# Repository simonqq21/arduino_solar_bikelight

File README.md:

# Arduino Solar Rear Bicycle Light 
## Main Hardware Components
- Arduino Nano
- 6V 1W solar panel 
- TP4056 li-ion charger with BMS chip 
- 18650 battery holder with 18650 battery x1  
- 10k resistor (charging input voltage divider)
- 50k resistor (charging input voltage divider) 
- 10k resistor (battery voltage divider)
- 50k resistor (battery panel voltage divider) 
- Diffused red LED x5 (dim light, one as a charging indicator when turned off)
- 150R resistor x5
- Clear red LED x4 (bright light) 
- 150R resistor x4
- 2N3904 NPN transistor x2
- 10k resistor x2
- Momentary pushbutton 

## Things to calculate/ measure: 
solar panel no-load voltage 
solar panel max current
expected battery charge time 
expected runtime 
voltage divider resistances 

assume 6V max voltage input, 5V max voltage output 
6 * r2 / (r1 + r2) = 5 
6 * r2 = 5 * (r1 + r2)
6 * r2 = 5 * r1 + 5 * r2 
r2 = 5 * r1 
The current through the voltage divider must be minimal. 
if r2 is 50k, r1 is 10k.

LED current limiting resistors 
diffused LED 

Li-ion voltage max 4.2V 
LED current = 20mA
(4.2-2.1)/0.02 = 105 R resistor minimum

clear LED

Li-ion voltage max 4.2V 
LED current = 30mA
(4.2-2.1)/0.03 = 70 R resistor minimum

Calculations for the voltage divider resistances when using the internal 1.1V Vref 

Min input (PV panel and USB charger) voltage: 0V
Max input (PV panel and USB charger) voltage: 7V
max USB charger voltage: 5V
max PV panel voltage: ~7V - 0.3V = 6.7V (0.3V voltage drop from the diode)
Max input (PV panel and USB charger) voltage: 6.7 ~= 7V
Vin = 7V 
Vout = 1.1V
7* r2/(r1+r2) = 1.1
7r2 = 1.1r1 + 1.1r2 
5.9r2 = 1.1r1 
r1 = 5.9r2/1.1
r2 = 10k 
r1 = 53636.364 ~= 53k 

Min battery voltage: 3.0V
Max battery voltage: 4.2V
Vin = 4.2V
Vout = 1.1V
4.2* r2/(r1+r2) = 1.1 
4.2r2 = 1.1r1 + 1.1r2 
3.1r2 = 1.1r1
r1 = 3.1r2 / 1.1 
r2 = 10k  
r1 = 28181.818 ~= 28k 

Battery voltage divider 
r1 = 50k 
r2 = 10k 
input voltage min: 3.0V
input voltage max: 4.2V
conversion factor = 10k/(50k+10k) = 1/6 
3.0V*1/6 = 0.5V 
4.2V*1/6 = 0.7V
0.5/1.1*1023=465 
0.7/1.1*1023=651

Charging input voltage divider 
r1 = 50k 
r2 = 10k 
input voltage min: 0.0V
input voltage max: 7.0V
input voltage threshold: 4.8V 
conversion factor = 10k/(50k+10k) = 1/6 
0.0V*1/6 = 0V 
7.0V*1/6 = 1.167V
4.8V*1/6 = 0.8V  
1.167/1.1*1023=1023 (capped at 1023, but it doesn't matter anyways)
0.8/1.1*1023=744

# Power Consumption 
power consumption in Off Mode (quiescent current) 35uA
power consumption in Low Mode 78mA
power consumption in High Mode 118mA

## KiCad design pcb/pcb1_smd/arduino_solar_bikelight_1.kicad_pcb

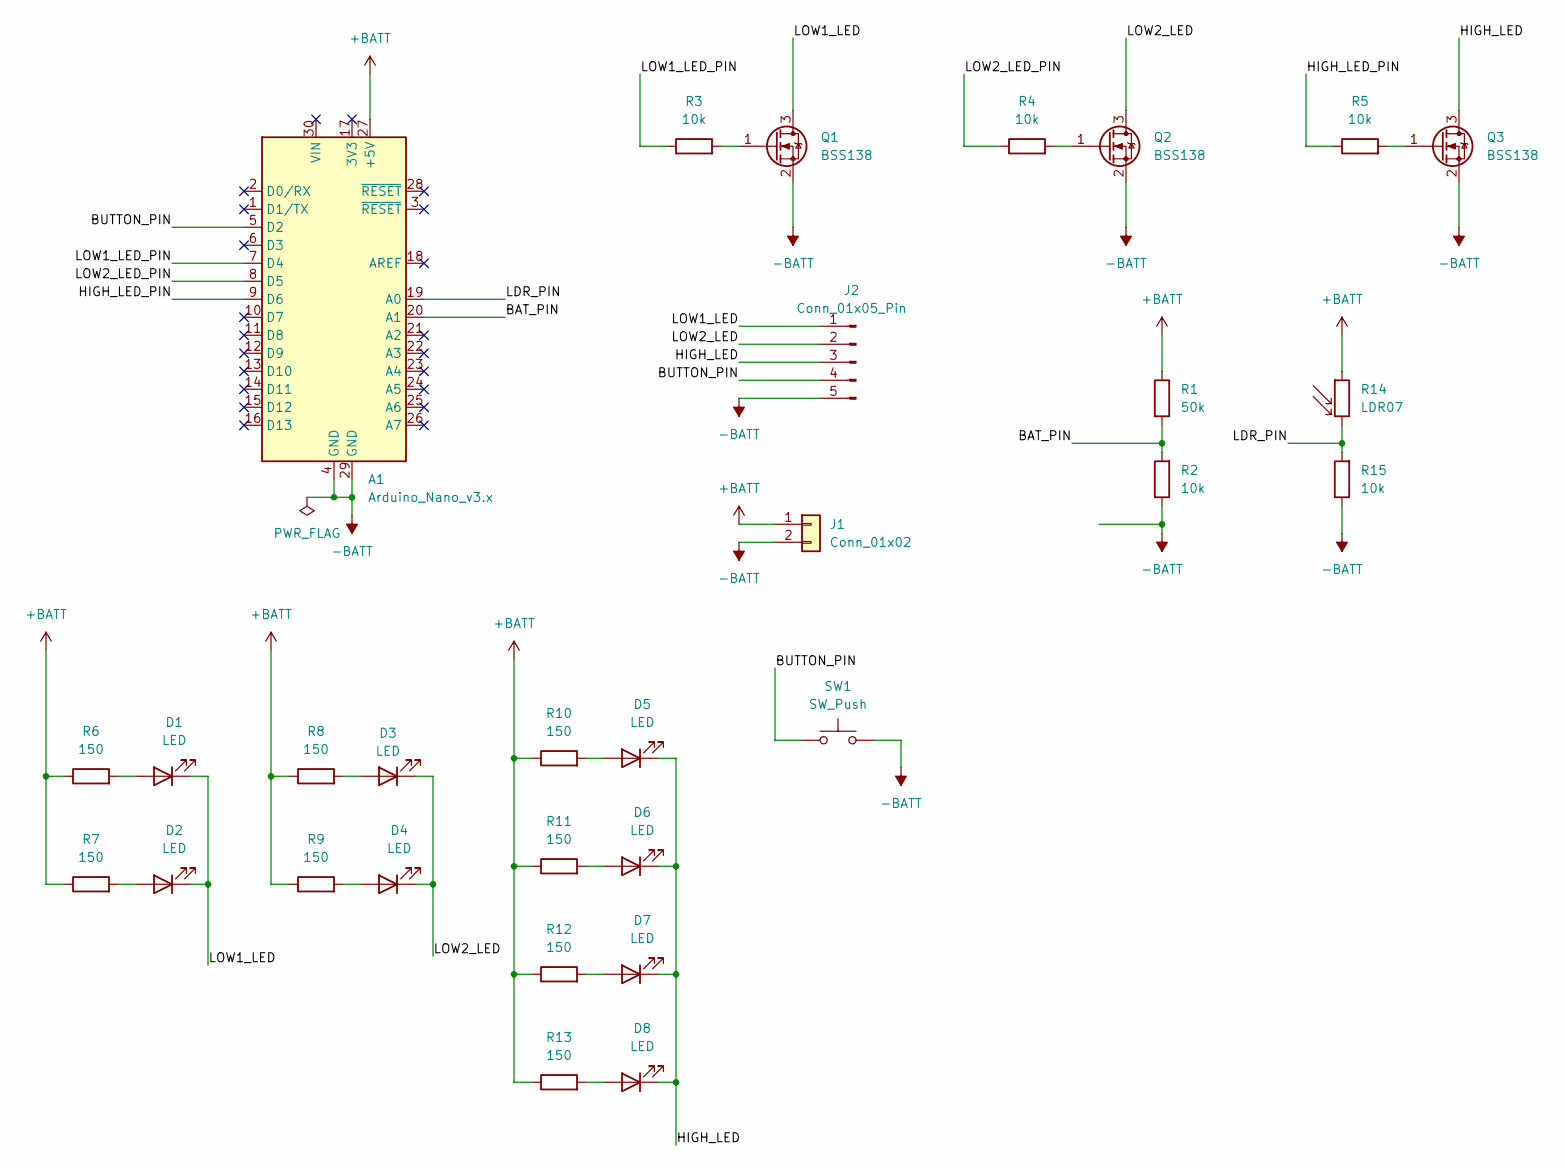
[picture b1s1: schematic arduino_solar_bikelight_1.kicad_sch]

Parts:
A1: Arduino_Nano_v3.x; Arduino_Nano
D1, D2, D3, D4, D5, D6, D7, D8: LED; LED_D5.0mm
J1: Conn_01x02; JST_XH_B2B-XH-AM_1x02_P2.50mm_Vertical
J2: Conn_01x05_Pin; PinHeader_1x05_P2.54mm_Vertical
Q1, Q2, Q3: BSS138; SOT-23; LCSC C78284
R1: 50k; R_0805_2012Metric_Pad1.20x1.40mm_HandSolder; LCSC C17737
R2, R3, R4, R5, R15: 10k; R_0805_2012Metric_Pad1.20x1.40mm_HandSolder; LCSC C17414
R6, R7, R8, R9, R10, R11, R12, R13: 150; R_0805_2012Metric_Pad1.20x1.40mm_HandSolder; LCSC C17471
R14: LDR07; R_LDR_5.1x4.3mm_P3.4mm_Vertical
SW1: SW_Push; SW_SPST_Omron_B3F-40xx

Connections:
+BATT: A1.27 (+5V), J1.1, R1.1, R6.1, R7.1, R8.1, R9.1, R10.1, R11.1, R12.1, R13.1, R14.1
-BATT: A1.4 (GND), A1.29 (GND), J1.2, J2.5, Q1.2 (S), Q2.2 (S), Q3.2 (S), R2.1, R15.1, SW1.2
/BAT_PIN: A1.20 (A1), R1.2, R2.2
/BUTTON_PIN: A1.5 (D2), J2.4, SW1.1
/HIGH_LED: D5.1 (K), D6.1 (K), D7.1 (K), D8.1 (K), J2.3, Q3.3 (D)
/HIGH_LED_PIN: A1.9 (D6), R5.1
/LDR_PIN: A1.19 (A0), R14.2, R15.2
/LOW1_LED: D1.1 (K), D2.1 (K), J2.1, Q1.3 (D)
/LOW1_LED_PIN: A1.7 (D4), R3.1
/LOW2_LED: D3.1 (K), D4.1 (K), J2.2, Q2.3 (D)
/LOW2_LED_PIN: A1.8 (D5), R4.1
unnamed: D1.2 (A), R6.2
unnamed: D2.2 (A), R7.2
unnamed: D3.2 (A), R8.2
unnamed: D4.2 (A), R9.2
unnamed: D5.2 (A), R10.2
unnamed: D6.2 (A), R11.2
unnamed: D7.2 (A), R12.2
unnamed: D8.2 (A), R13.2
unnamed: Q1.1 (G), R3.2
unnamed: Q2.1 (G), R4.2
unnamed: Q3.1 (G), R5.2

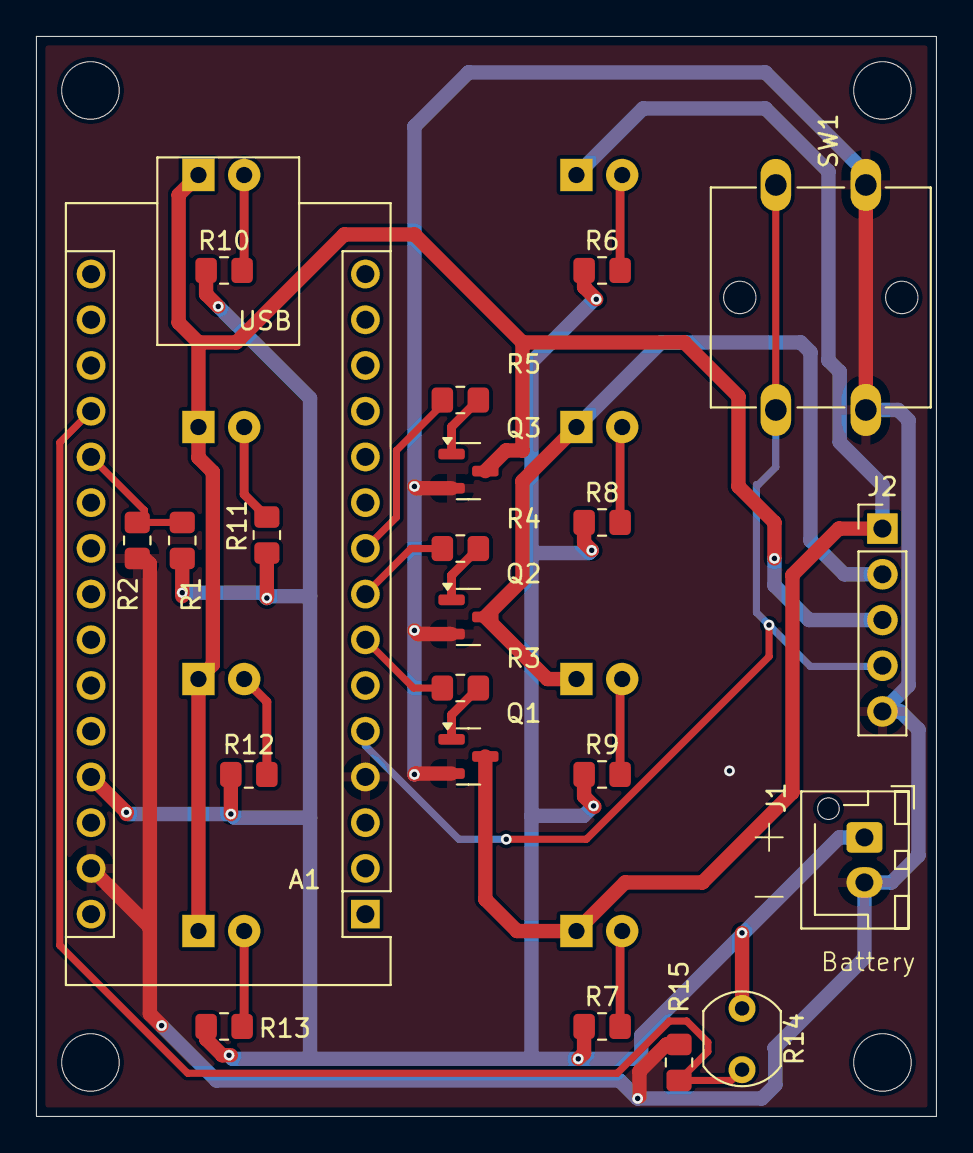
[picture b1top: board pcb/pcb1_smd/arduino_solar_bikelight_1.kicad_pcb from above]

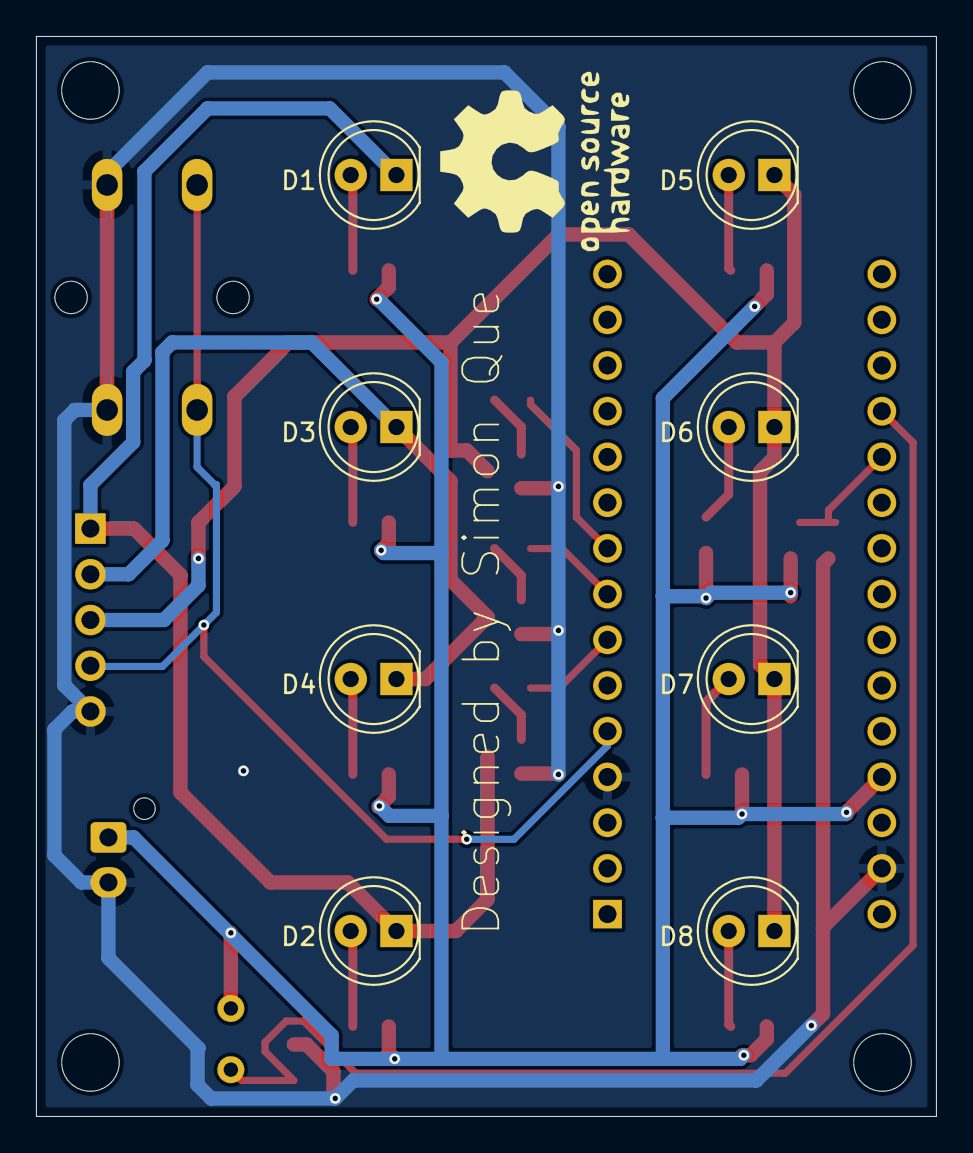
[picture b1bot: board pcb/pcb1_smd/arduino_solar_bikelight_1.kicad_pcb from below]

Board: 2 copper layers, 50.0 x 60.0 mm, 30 parts (8 on the bottom side), 22 nets.

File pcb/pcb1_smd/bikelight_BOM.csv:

Designator,Comment,Footprint,LCSC
"R6,R7,R8,R9,R10,R11,R12,R13",150,Resistor_SMD:R_0805_2012Metric_Pad1.20x1.40mm_HandSolder,C17471
"R2,R3,R4,R5",10k,Resistor_SMD:R_0805_2012Metric_Pad1.20x1.40mm_HandSolder,C17414
R1,50k,Resistor_SMD:R_0805_2012Metric_Pad1.20x1.40mm_HandSolder,C17737
A1,Arduino_Nano_v3.x,Module:Arduino_Nano,
"Q1,Q2,Q3",BSS138,Package_TO_SOT_SMD:SOT-23,C78284
J1,Conn_01x02,Connector_JST:JST_XH_B2B-XH-AM_1x02_P2.50mm_Vertical,
J2,Conn_01x05_Pin,Connector_PinHeader_2.54mm:PinHeader_1x05_P2.54mm_Vertical,
"D1,D2,D3,D4,D5,D6,D7,D8",LED,LED_THT:LED_D5.0mm,
SW1,SW_Push,Button_Switch_THT:SW_SPST_Omron_B3F-40xx,

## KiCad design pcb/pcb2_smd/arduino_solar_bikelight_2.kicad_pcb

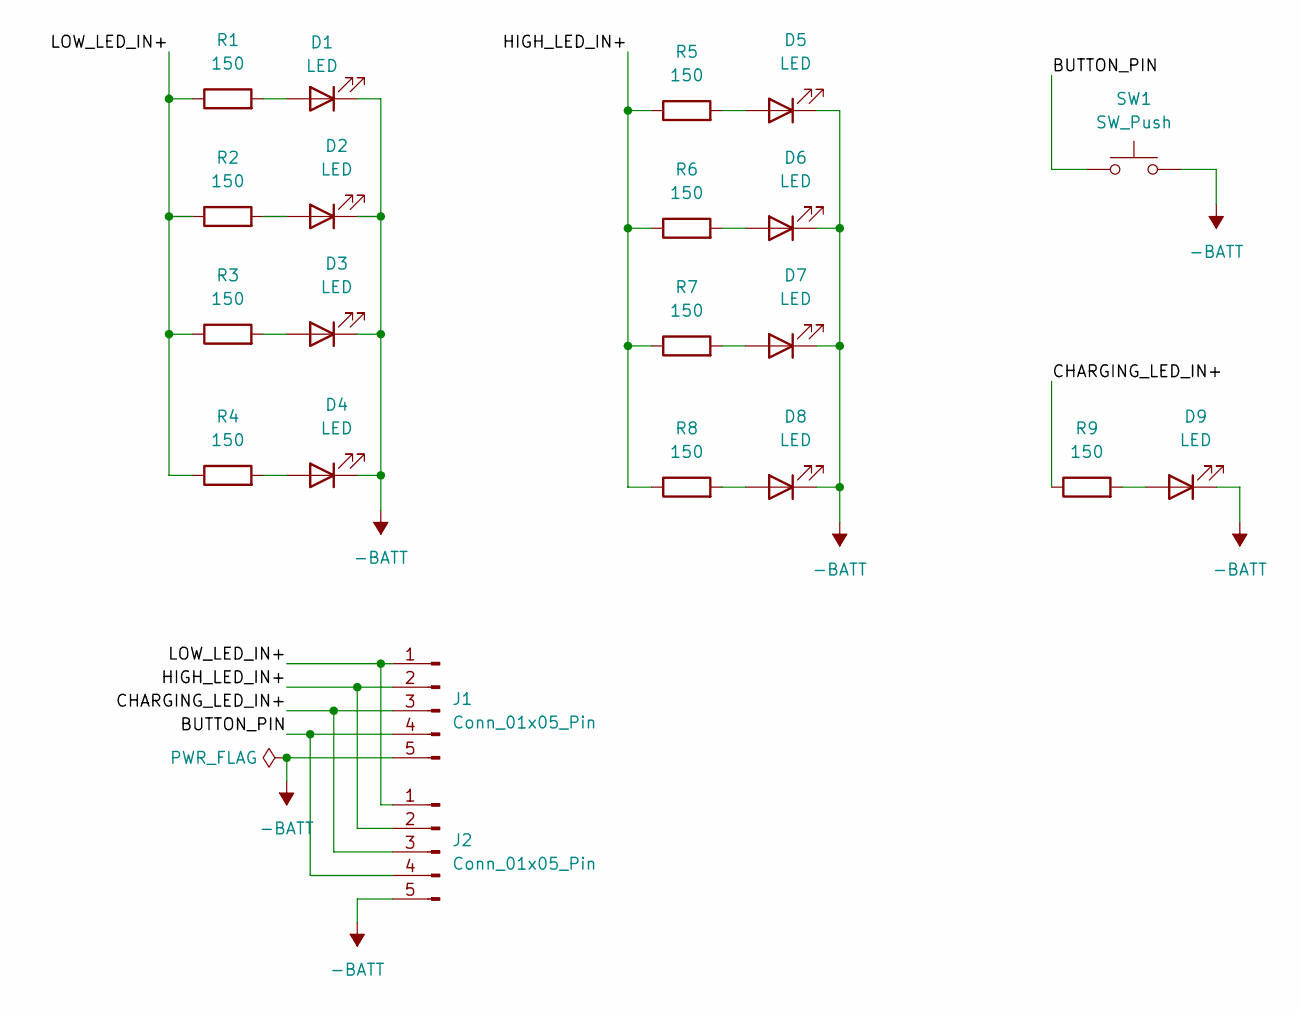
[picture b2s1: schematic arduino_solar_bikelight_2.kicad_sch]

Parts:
D1, D2, D3, D4, D5, D6, D7, D8, D9: LED; LED_D5.0mm
J1, J2: Conn_01x05_Pin; PinSocket_1x05_P2.54mm_Vertical
R1, R2, R3, R4, R5, R6, R7, R8, R9: 150; R_Axial_DIN0207_L6.3mm_D2.5mm_P10.16mm_Horizontal
SW1: SW_Push; SW_SPST_Omron_B3F-40xx

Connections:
-BATT: D1.1 (K), D2.1 (K), D3.1 (K), D4.1 (K), D5.1 (K), D6.1 (K), D7.1 (K), D8.1 (K), D9.1 (K), J1.5, J2.5, SW1.2
/BUTTON_PIN: J1.4, J2.4, SW1.1
/CHARGING_LED_IN+: J1.3, J2.3, R9.1
/HIGH_LED_IN+: J1.2, J2.2, R5.1, R6.1, R7.1, R8.1
/LOW_LED_IN+: J1.1, J2.1, R1.1, R2.1, R3.1, R4.1
unnamed: D1.2 (A), R1.2
unnamed: D2.2 (A), R2.2
unnamed: D3.2 (A), R3.2
unnamed: D4.2 (A), R4.2
unnamed: D5.2 (A), R5.2
unnamed: D6.2 (A), R6.2
unnamed: D7.2 (A), R7.2
unnamed: D8.2 (A), R8.2
unnamed: D9.2 (A), R9.2

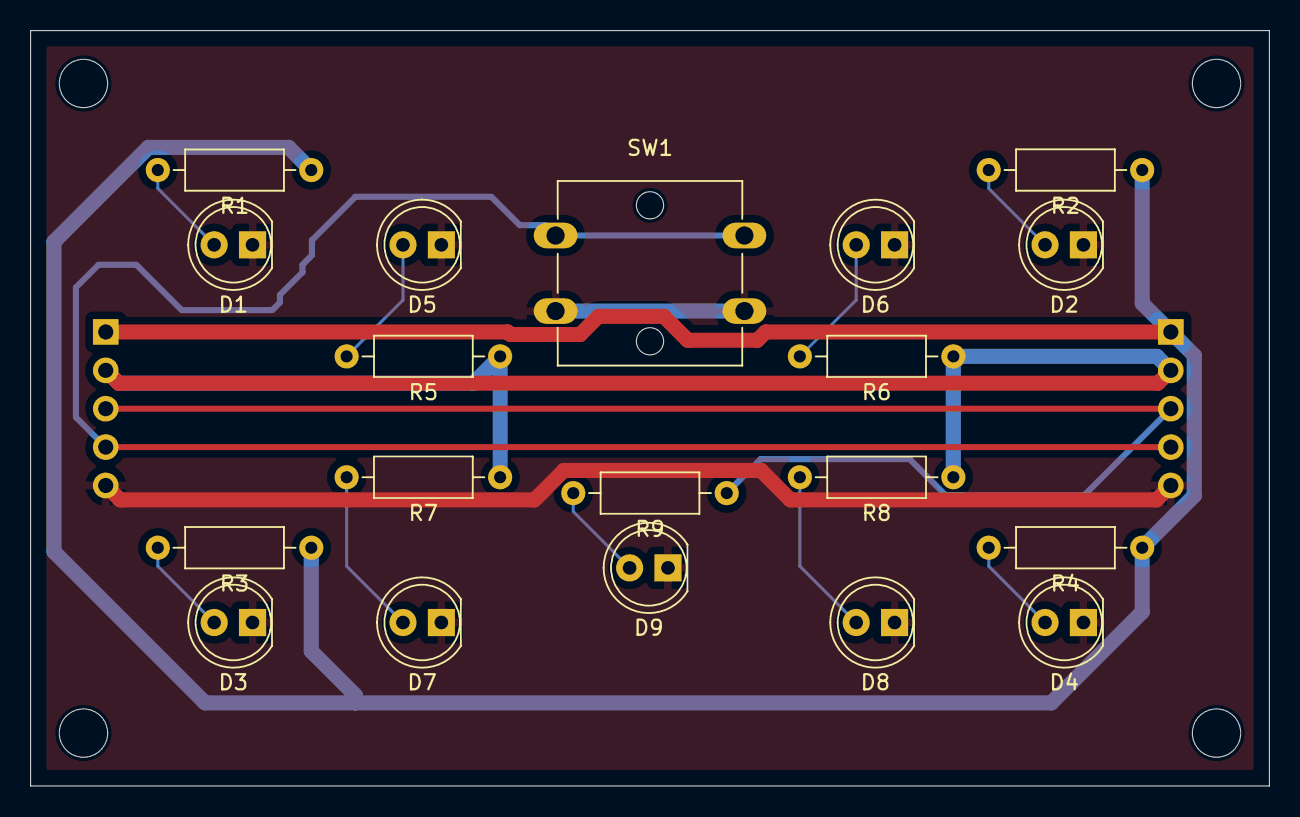
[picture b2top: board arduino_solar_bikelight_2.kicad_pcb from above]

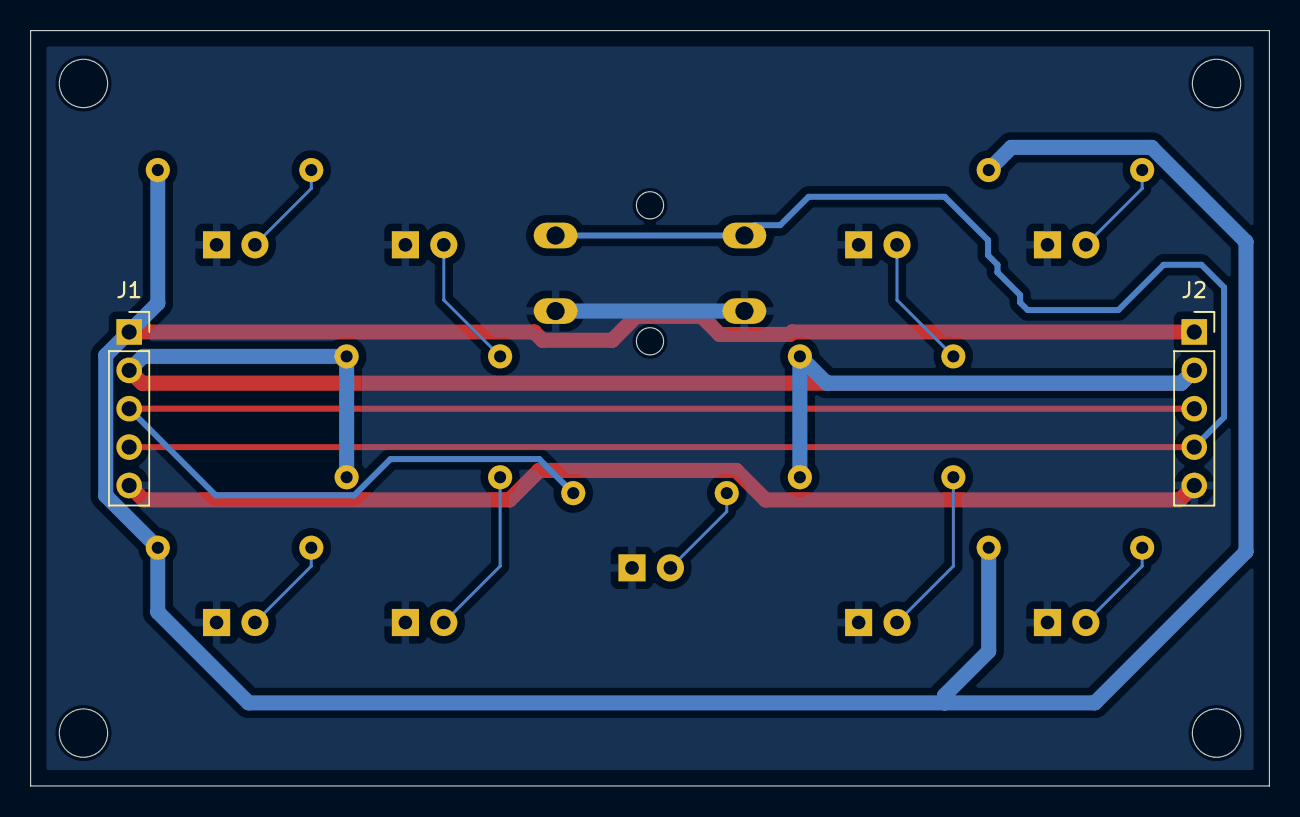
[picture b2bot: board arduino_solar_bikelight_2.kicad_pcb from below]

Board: 2 copper layers, 82.0 x 50.0 mm, 21 parts (2 on the bottom side), 14 nets.

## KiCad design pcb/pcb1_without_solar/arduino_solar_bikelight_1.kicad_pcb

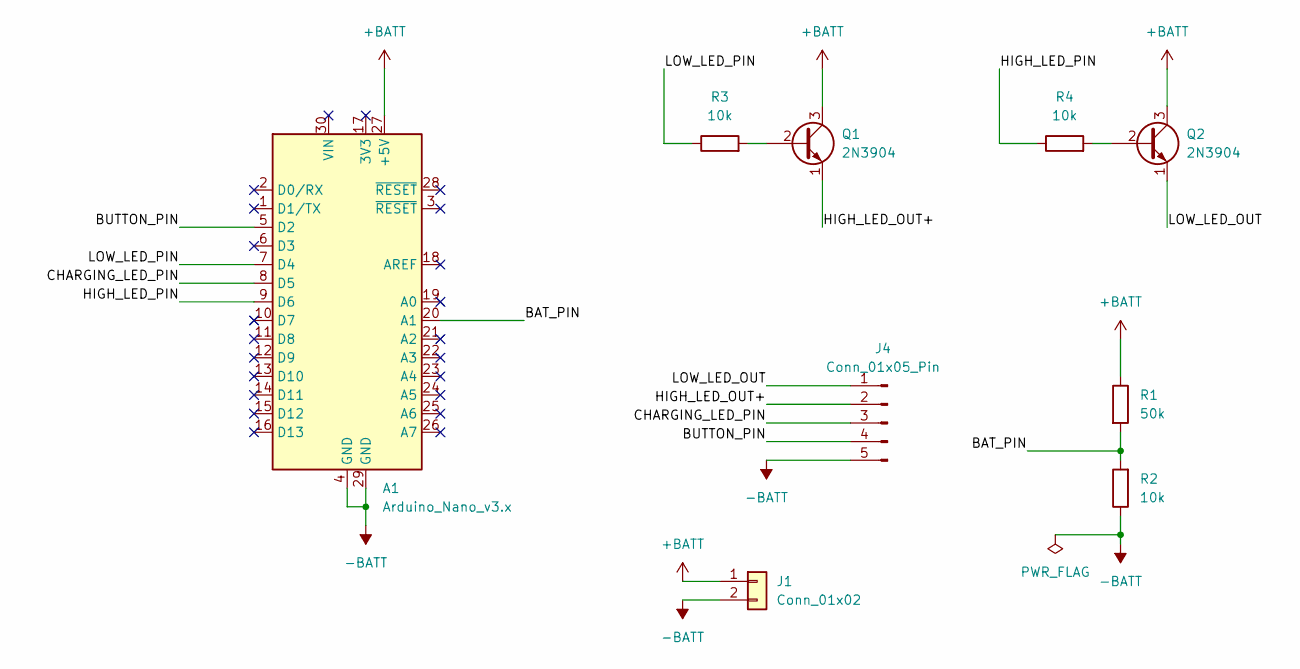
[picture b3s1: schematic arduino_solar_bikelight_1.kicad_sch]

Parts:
A1: Arduino_Nano_v3.x; Arduino_Nano
J1: Conn_01x02; JST_XH_B2B-XH-AM_1x02_P2.50mm_Vertical
J4: Conn_01x05_Pin; PinHeader_1x05_P2.54mm_Vertical
Q1, Q2: 2N3904; TO-92_Inline
R1: 50k; R_Axial_DIN0207_L6.3mm_D2.5mm_P10.16mm_Horizontal
R2, R3, R4: 10k; R_Axial_DIN0207_L6.3mm_D2.5mm_P10.16mm_Horizontal

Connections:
+BATT: A1.27 (+5V), J1.1, Q1.3 (C), Q2.3 (C), R1.1
-BATT: A1.4 (GND), A1.29 (GND), J1.2, J4.5, R2.1
/BAT_PIN: A1.20 (A1), R1.2, R2.2
/BUTTON_PIN: A1.5 (D2), J4.4
/CHARGING_LED_PIN: A1.8 (D5), J4.3
/HIGH_LED_OUT+: J4.2, Q1.1 (E)
/HIGH_LED_PIN: A1.9 (D6), R4.1
/LOW_LED_OUT: J4.1, Q2.1 (E)
/LOW_LED_PIN: A1.7 (D4), R3.1
unnamed: Q1.2 (B), R3.2
unnamed: Q2.2 (B), R4.2

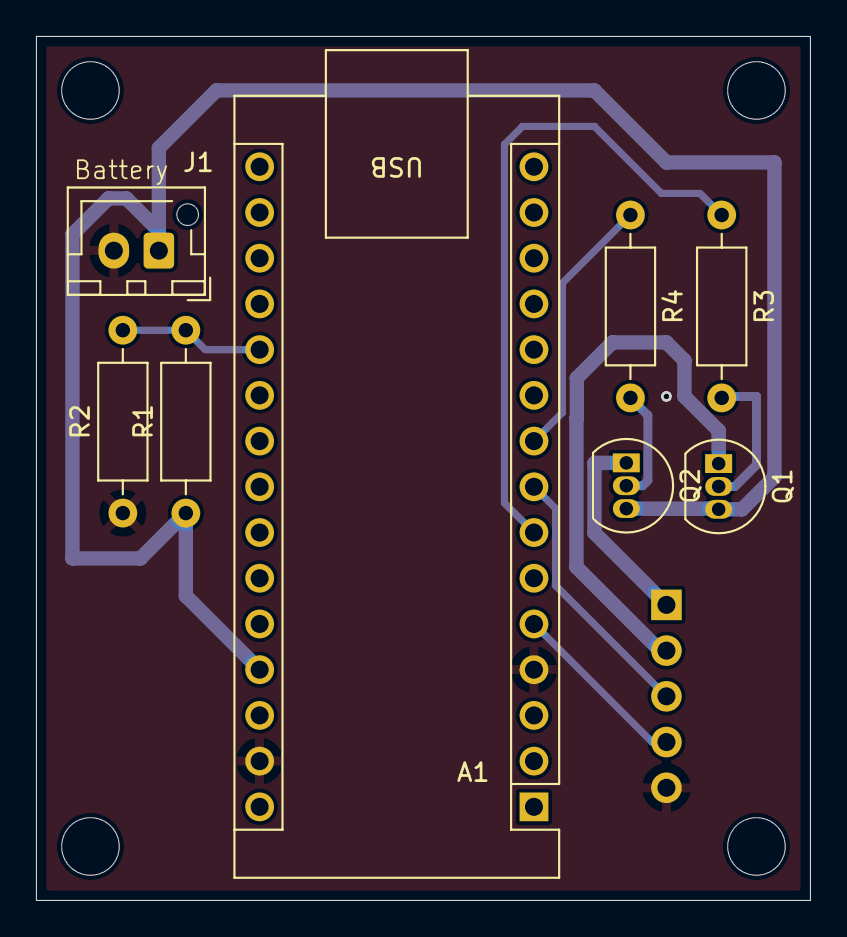
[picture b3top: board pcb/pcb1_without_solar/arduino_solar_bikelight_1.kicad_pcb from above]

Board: 2 copper layers, 43.0 x 48.0 mm, 9 parts (1 on the bottom side), 11 nets.

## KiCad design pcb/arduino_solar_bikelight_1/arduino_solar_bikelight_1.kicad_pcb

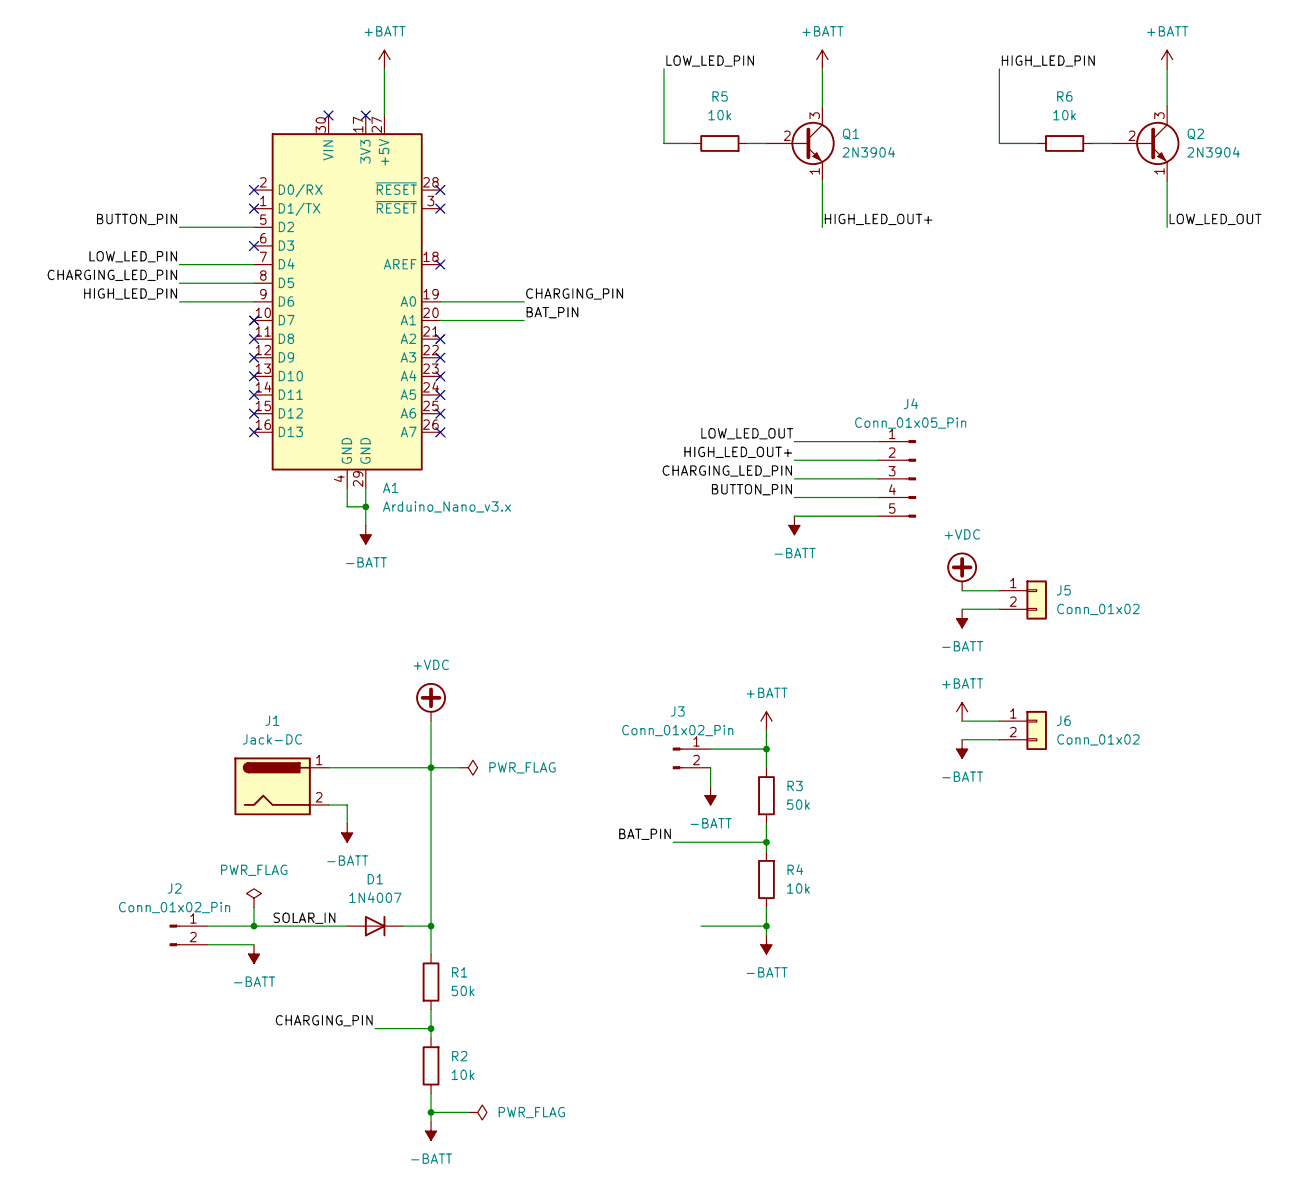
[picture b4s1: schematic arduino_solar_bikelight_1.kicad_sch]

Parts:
A1: Arduino_Nano_v3.x; Arduino_Nano
D1: 1N4007; D_DO-41_SOD81_P10.16mm_Horizontal
J1: Jack-DC; BarrelJack_GCT_DCJ200-10-A_Horizontal
J2, J3: Conn_01x02_Pin; JST_XH_B2B-XH-A_1x02_P2.50mm_Vertical
J4: Conn_01x05_Pin; PinHeader_1x05_P2.54mm_Vertical
J5, J6: Conn_01x02; PinHeader_2x01_P2.54mm_Vertical
Q1, Q2: 2N3904; TO-92_Inline
R1, R3: 50k; R_Axial_DIN0207_L6.3mm_D2.5mm_P10.16mm_Horizontal
R2, R4, R5, R6: 10k; R_Axial_DIN0207_L6.3mm_D2.5mm_P10.16mm_Horizontal

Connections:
+BATT: A1.27 (+5V), J3.1, J6.1, Q1.3 (C), Q2.3 (C), R3.1
+VDC: D1.1 (K), J1.1, J5.1, R1.1
-BATT: A1.4 (GND), A1.29 (GND), J1.2, J2.2, J3.2, J4.5, J5.2, J6.2, R2.1, R4.1
/BAT_PIN: A1.20 (A1), R3.2, R4.2
/BUTTON_PIN: A1.5 (D2), J4.4
/CHARGING_LED_PIN: A1.8 (D5), J4.3
/CHARGING_PIN: A1.19 (A0), R1.2, R2.2
/HIGH_LED_OUT+: J4.2, Q1.1 (E)
/HIGH_LED_PIN: A1.9 (D6), R6.1
/LOW_LED_OUT: J4.1, Q2.1 (E)
/LOW_LED_PIN: A1.7 (D4), R5.1
/SOLAR_IN: D1.2 (A), J2.1
unnamed: Q1.2 (B), R5.2
unnamed: Q2.2 (B), R6.2

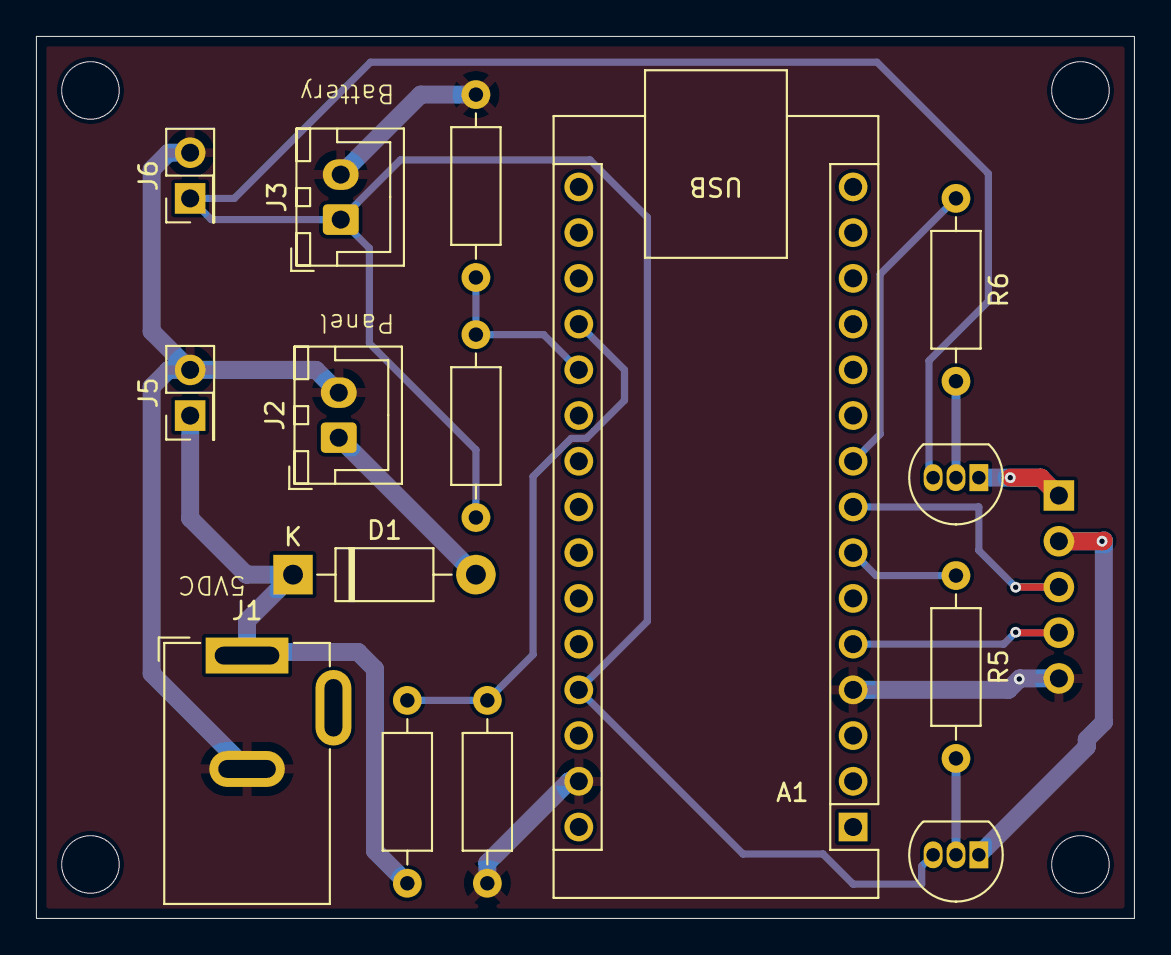
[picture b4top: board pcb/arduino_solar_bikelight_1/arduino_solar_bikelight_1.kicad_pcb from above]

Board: 2 copper layers, 61.0 x 49.0 mm, 16 parts (1 on the bottom side), 14 nets.

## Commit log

2025-01-09 initial codes
2025-01-12 working arduino code, but needs power consumption optimization and code cleanup
2025-01-15 working sleep mode but charging LED isn't working when sleeping
2025-01-15 abcd
2025-01-15 working sleep mode and watchdog timer with charging LED working in deepsleep
2025-01-15 fixed bug where clicking button when off sends it directly to mode 2 because of button bouncing
2025-01-16 comments set WDT interrupt to 4s
2025-01-16 initial calculations for initial BOM, testing measurements to follow
2025-01-20 pio upload using Arduino as ISP
2025-01-21 calculations for voltage dividers using 1v1 Vref
2025-01-21 two voltage dividers: 1 for charging and another for battery low voltage cutoff improved charging indicator LED behavior added an extended low mode
2025-01-21 fixed bug with low battery mode not turning off when button is pressed
2025-01-22 working low battery mode
2025-01-22 working doubleclick function to toggle autoMode working led indication for autoMode TODO: change light behavior based on autoMode save autoMode to EEPROM
2025-01-23 fixed bug with charging LED not working when sleeping
2025-01-23 put button shortclick function in button wakeup ISR instead of hardcoding curMode=1
2025-01-23 djdjd
2025-01-23 working code, will test some more in the following days and make edits when needed.
2025-01-24 fixed bug with automatic drop down to extended low mode on low battery detection
2025-01-24 added hysteresis to low battery detection at button press to smooth out the voltage spikes caused by the LEDs switching
2025-01-24 added averaging code for ADC so that a sudden dip or spike won't create a false low battery or dead battery event Improved the stability of the system added dead battery condition to checkAutoMode to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
2025-01-24 fixed bug where the mode is set to zero when battery is low but not dead.
2025-01-24 added some code to disable ADC while sleeping
2025-01-26 started work on PCB
2025-01-27 placed components in schematic and assigned footprints
2025-01-29 completed PCB1 currently working on PCB2
2025-02-08 updated schematic and pcb to have a non solar, non charging version for simplicity exported svg, gerber, and pdf files
2025-02-09 gerbergerber
2025-02-10 added smd version with mosfets in place of bjts
2025-02-10 completed the latest updated design of the PCB with SMT parts and MOSFETs
2025-02-12 learned how to export BOM and CPL and gerbers added graphics and text at the back silkscreen
2025-02-13 added LDR to board and exported to production
2025-03-05 battery box 3d model
2025-03-05 lowleds2
2025-03-06 skibiditoilet
2025-03-06 added dynamo mode, removed unused code, and currently defining updated logic
2025-03-07 defined behavior for lighting modes, memory modes, and light sensing auto mode
2025-03-07 on off separated from light modes
2025-03-08 created config struct for nonvolatile configuration created functions to save and load nonvolatile config
2025-03-08 working mode memory settings TODO: indicator LED to indicate the current mode memory mode and auto mode setting
2025-03-09 working ontification logic working mode memory logic
2025-03-09 asdfghjk
2025-03-12 fixed bugs in sleep mode behavior and long press to turn on (and wake up from sleep)
2025-03-13 changed wakeupISR interrupt mode from FALLING to LOW
2025-03-17 updated mode memory behavior so that the power state is saved in the EEPROM.
2025-03-20 3d printed models fixed code to save config to EEPROM when the light is waken up by long press from sleep.
2025-04-01 asedfnkl;sdvb[
